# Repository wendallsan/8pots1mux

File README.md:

# 8pots1mux
Here's a super-basic PCB designed to use a CD4051 multiplexor IC to send 8 pot values to your microcontroller (or whatever) of choice!  I've been using them in Daisy Seed and Rasperry Pi Pico projects, they're fun!  

Required components (plus Tayda or Mouser links, current as of 2023/08/09):  

- 8x [9mm vertical potentiomenters 100k linear taper](https://www.taydaelectronics.com/100k-ohm-linear-taper-potentiometer-round-knurled-plastic-shaft-pcb-9mm.html)-- like the stuff used in Eurorack!  
- 1x [10nF 0805 capacitor  ](https://www.taydaelectronics.com/10nf-50v-smd-ceramic-chip-capacitor.html)  
- 1x [CD4051 SOIC-Narrow-16 IC](https://www.mouser.com/ProductDetail/Texas-Instruments/CD4051BM96?qs=0le1rQK8zxqMHlJa1GNAzQ%3D%3D)    
- 1x 6 pin 2.54mm spaced connector of your choice ([maybe something like this](https://www.taydaelectronics.com/6-pin-2-54mm-single-row-female-pin-header.html)).

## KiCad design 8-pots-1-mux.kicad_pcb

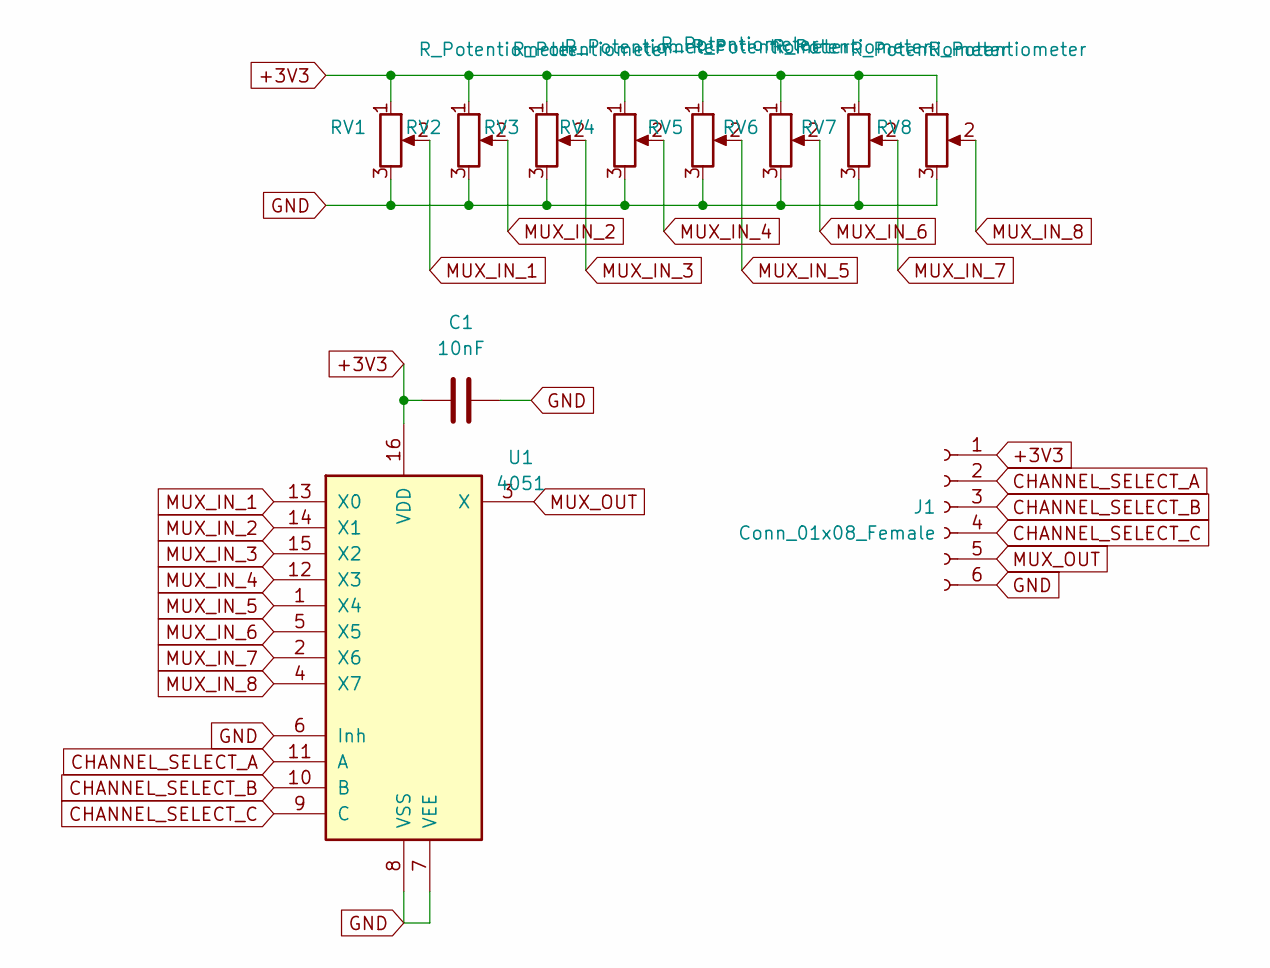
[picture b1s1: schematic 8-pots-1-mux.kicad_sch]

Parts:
C1: 10nF; C_0805_2012Metric
J1: Conn_01x08_Female; PinSocket_1x06_P2.54mm_Horizontal
RV1, RV2, RV3, RV4, RV5, RV6, RV7, RV8: R_Potentiometer; Potentiometer_Alpha_RD901F-40-00D_Single_Vertical
U1: 4051; SOIC-16_3.9x9.9mm_P1.27mm

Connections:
+3V3: C1.1, J1.1, RV1.1, RV2.1, RV3.1, RV4.1, RV5.1, RV6.1, RV7.1, RV8.1, U1.16 (VDD)
CHANNEL_SELECT_A: J1.2, U1.11 (A)
CHANNEL_SELECT_B: J1.3, U1.10 (B)
CHANNEL_SELECT_C: J1.4, U1.9 (C)
GND: C1.2, J1.6, RV1.3, RV2.3, RV3.3, RV4.3, RV5.3, RV6.3, RV7.3, RV8.3, U1.6 (Inh), U1.7 (VEE), U1.8 (VSS)
MUX_IN_1: RV1.2, U1.13 (X0)
MUX_IN_2: RV2.2, U1.14 (X1)
MUX_IN_3: RV3.2, U1.15 (X2)
MUX_IN_4: RV4.2, U1.12 (X3)
MUX_IN_5: RV5.2, U1.1 (X4)
MUX_IN_6: RV6.2, U1.5 (X5)
MUX_IN_7: RV7.2, U1.2 (X6)
MUX_IN_8: RV8.2, U1.4 (X7)
MUX_OUT: J1.5, U1.3 (X)

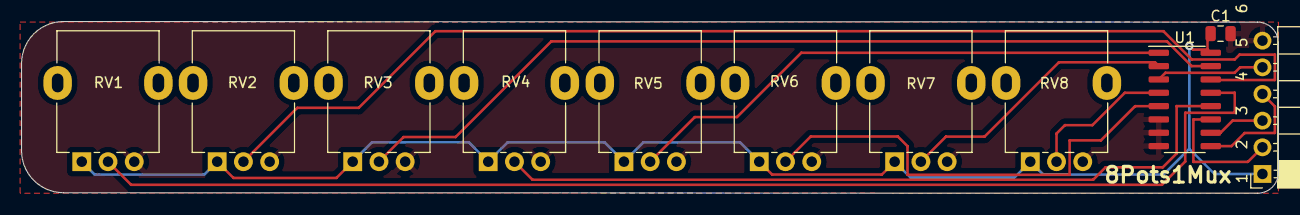
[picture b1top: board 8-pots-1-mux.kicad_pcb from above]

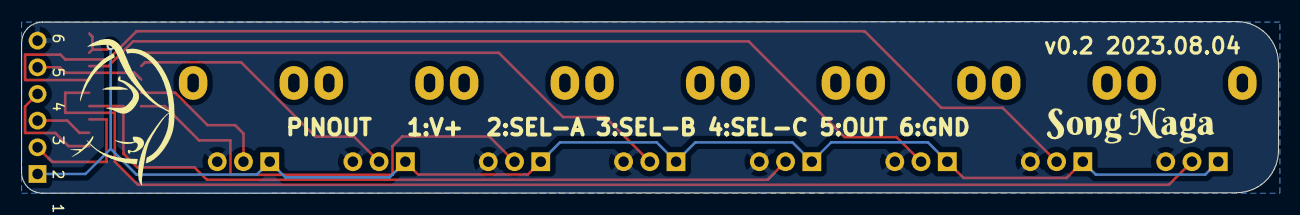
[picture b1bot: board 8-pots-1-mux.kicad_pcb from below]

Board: 2 copper layers, 119.7 x 16.4 mm, 13 parts (2 on the bottom side), 14 nets.

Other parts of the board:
G1, G2: LOGO
